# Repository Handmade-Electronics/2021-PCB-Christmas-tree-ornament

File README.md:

# 2021 Snowflake PCB Christmas tree ornament
 Snowflake shaped PCB Christmas tree ornament using a rechargable LIPO battery that recharcges via USB

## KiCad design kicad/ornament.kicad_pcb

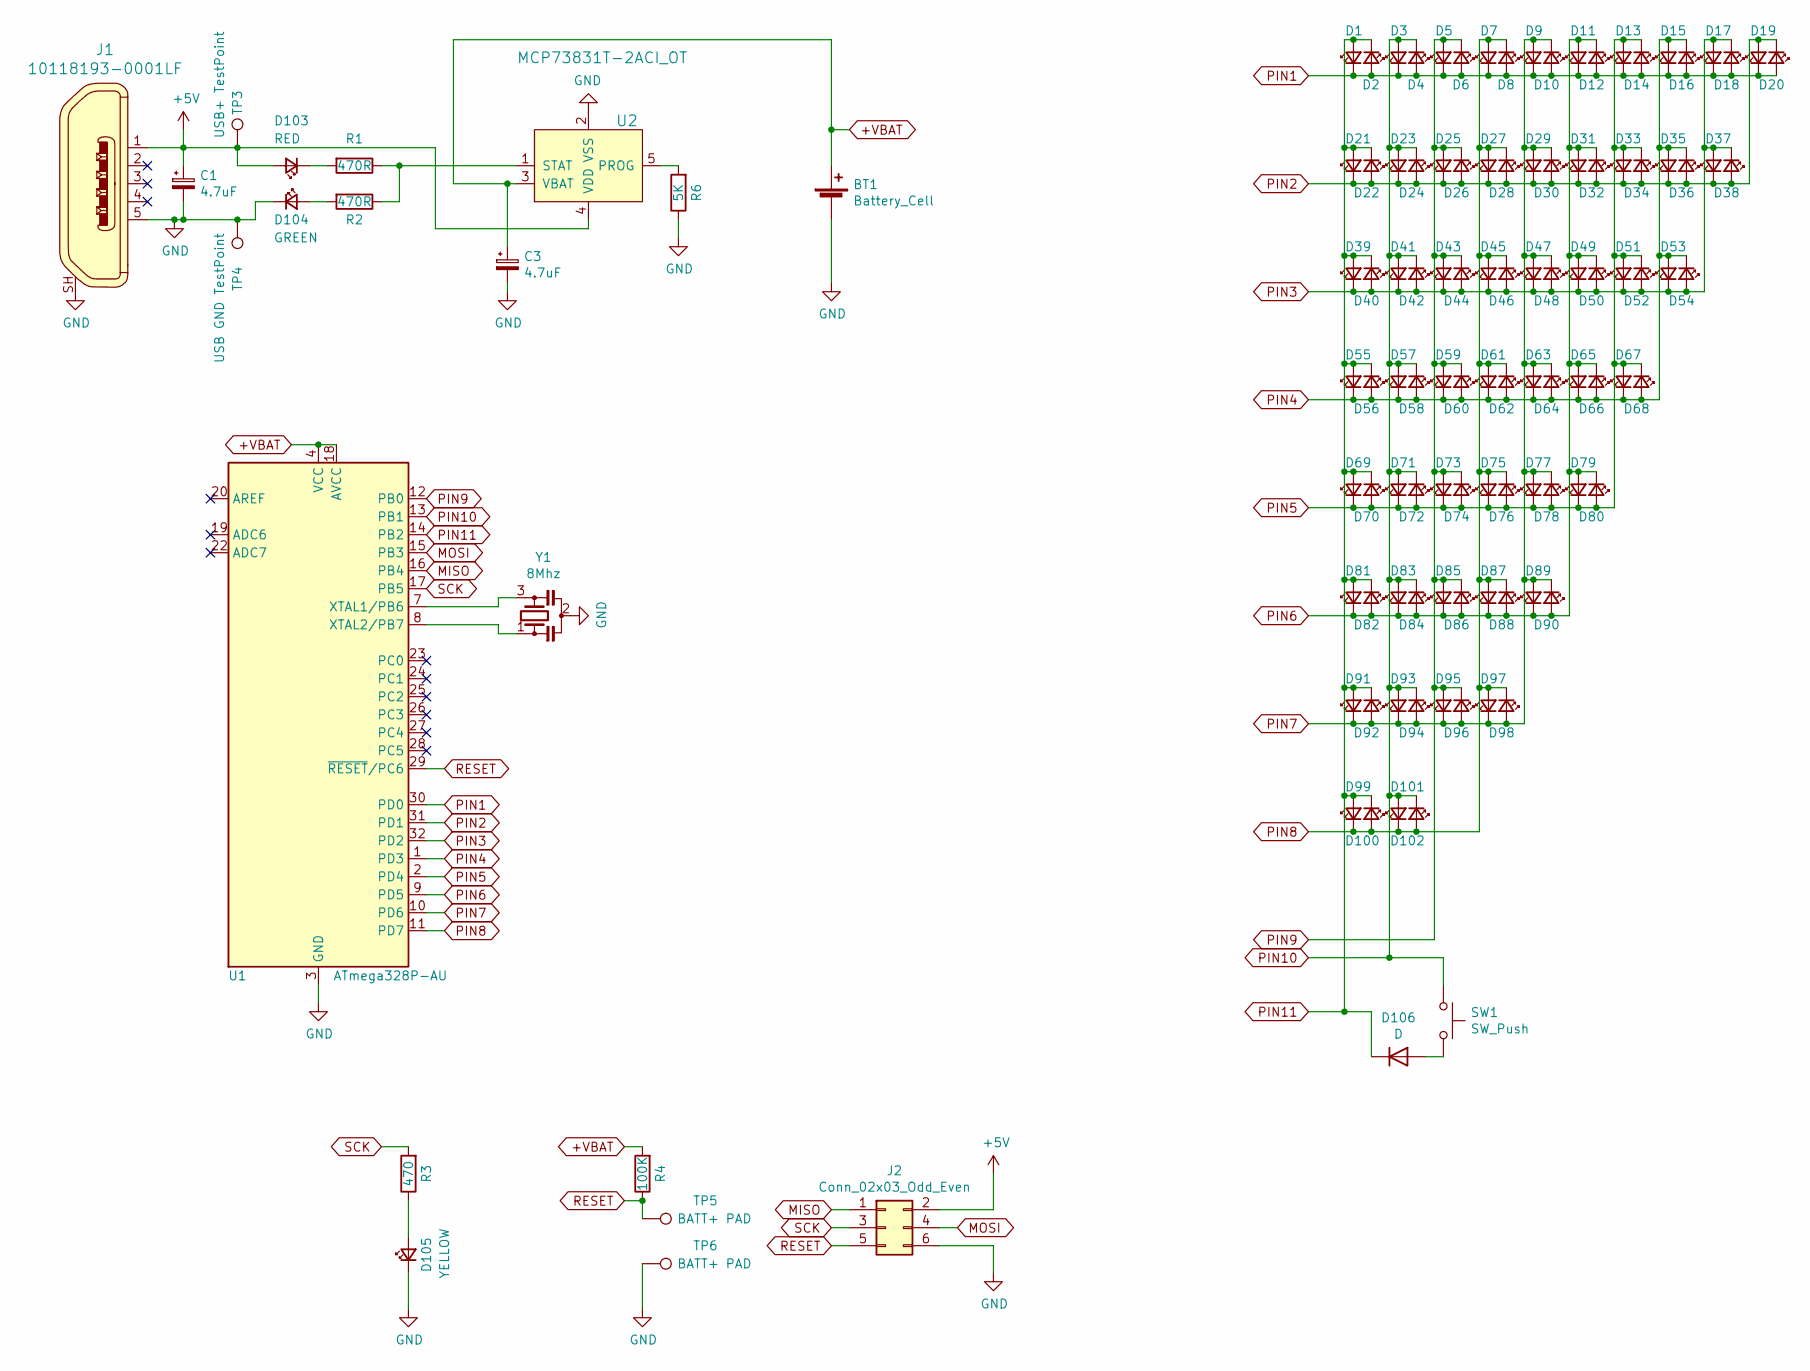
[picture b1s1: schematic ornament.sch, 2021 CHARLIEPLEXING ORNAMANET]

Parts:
BT1: Battery_Cell; LIPO_1S_503030_450mAH
C1, C3: 4.7uF; C_0603_1608Metric_Pad1.08x0.95mm_HandSolder
D1, D2, D3, D4, D5, D6, D7, D8, D9, D10, D11, D12, D13, D14, D15, D16, D17, D18, D19, D20, D21, D22, D23, D24, D25, D26, D27, D28, D29, D30, D31, D32, D33, D34, D35, D36, D37, D38, D39, D40, D41, D42, D43, D44, D45, D46, D47, D48, D49, D50, D51, D52, D53, D54, D55, D56, D57, D58, D59, D60, D61, D62, D63, D64, D65, D66, D67, D68, D69, D70, D71, D72, D73, D74, D75, D76, D77, D78, D79, D80, D81, D82, D83, D84, D85, D86, D87, D88, D89, D90, D91, D92, D93, D94, D95, D96, D97, D98, D99, D100, D101, D102: LED_Small; LED_0805_2012Metric
D103: RED; D_0603_1608Metric
D104: GREEN; D_0603_1608Metric
D105: YELLOW; D_0603_1608Metric
D106: D; D_0603_1608Metric
J1: 10118193-0001LF; USB_Micro_B_Female_10118192; MPN 10118193-0001LF; Digi-Key_PN 609-4616-1-ND
J2: Conn_02x03_Odd_Even; 6Pin_ICSP_Pads
R1, R2: 470R; R_0603_1608Metric
R3: 470; R_0603_1608Metric
R4: 100K; R_0603_1608Metric
R6: 5K; R_0603_1608Metric
SW1: SW_Push; SW_Push_1P1T_NO_6x6mm_H5.0mm(LCSC#C620316)
TP3: USB+ TestPoint; POGO_CONTACT_PAD_3MM
TP4: USB GND TestPoint; POGO_CONTACT_PAD_3MM
TP5, TP6: BATT+ PAD; TestPoint_Pad_2.0x2.0mm
U1: ATmega328P-AU; TQFP-32_7x7mm_P0.8mm
U2: MCP73831T-2ACI_OT; SOT-753; MPN MCP73831T-2ACI/OT; Digi-Key_PN MCP73831T-2ACI/OTCT-ND
Y1: 8Mhz; 3.7x3.1mm_Resonator

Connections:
+5V: C1.1, D103.2 (A), J1.1, J2.2, TP3.1, U2.4 (VDD)
+VBAT: BT1.1 (+), C3.1, R4.2, U1.4 (VCC), U1.6 (VCC), U1.18 (AVCC), U2.3 (VBAT)
GND: BT1.2 (-), C1.2, C3.2, D104.1 (K), D105.1 (K), J1.5, J1.SH, J2.6, R6.1, TP4.1, TP6.1, U1.3 (GND), U1.5 (GND), U1.21 (GND), U2.2 (VSS), Y1.2
MISO: J2.1, U1.16 (PB4)
MOSI: J2.4, U1.15 (PB3)
unnamed: D103.1 (K), R1.2
unnamed: D104.2 (A), R2.2
unnamed: D105.2 (A), R3.1
unnamed: D106.2 (A), SW1.2
unnamed: R1.1, R2.1, U2.1 (STAT)
unnamed: R6.2, U2.5 (PROG)
unnamed: U1.7 (XTAL1/PB6), Y1.3
unnamed: U1.8 (XTAL2/PB7), Y1.1
PIN1: D1.1 (K), D2.2 (A), D3.1 (K), D4.2 (A), D5.1 (K), D6.2 (A), D7.1 (K), D8.2 (A), D9.1 (K), D10.2 (A), D11.1 (K), D12.2 (A), D13.1 (K), D14.2 (A), D15.1 (K), D16.2 (A), D17.1 (K), D18.2 (A), D19.1 (K), D20.2 (A), U1.30 (PD0)
PIN2: D19.2 (A), D20.1 (K), D21.1 (K), D22.2 (A), D23.1 (K), D24.2 (A), D25.1 (K), D26.2 (A), D27.1 (K), D28.2 (A), D29.1 (K), D30.2 (A), D31.1 (K), D32.2 (A), D33.1 (K), D34.2 (A), D35.1 (K), D36.2 (A), D37.1 (K), D38.2 (A), U1.31 (PD1)
PIN3: D17.2 (A), D18.1 (K), D37.2 (A), D38.1 (K), D39.1 (K), D40.2 (A), D41.1 (K), D42.2 (A), D43.1 (K), D44.2 (A), D45.1 (K), D46.2 (A), D47.1 (K), D48.2 (A), D49.1 (K), D50.2 (A), D51.1 (K), D52.2 (A), D53.1 (K), D54.2 (A), U1.32 (PD2)
PIN4: D15.2 (A), D16.1 (K), D35.2 (A), D36.1 (K), D53.2 (A), D54.1 (K), D55.1 (K), D56.2 (A), D57.1 (K), D58.2 (A), D59.1 (K), D60.2 (A), D61.1 (K), D62.2 (A), D63.1 (K), D64.2 (A), D65.1 (K), D66.2 (A), D67.1 (K), D68.2 (A), U1.1 (PD3)
PIN5: D13.2 (A), D14.1 (K), D33.2 (A), D34.1 (K), D51.2 (A), D52.1 (K), D67.2 (A), D68.1 (K), D69.1 (K), D70.2 (A), D71.1 (K), D72.2 (A), D73.1 (K), D74.2 (A), D75.1 (K), D76.2 (A), D77.1 (K), D78.2 (A), D79.1 (K), D80.2 (A), U1.2 (PD4)
PIN6: D11.2 (A), D12.1 (K), D31.2 (A), D32.1 (K), D49.2 (A), D50.1 (K), D65.2 (A), D66.1 (K), D79.2 (A), D80.1 (K), D81.1 (K), D82.2 (A), D83.1 (K), D84.2 (A), D85.1 (K), D86.2 (A), D87.1 (K), D88.2 (A), D89.1 (K), D90.2 (A), U1.9 (PD5)
PIN7: D9.2 (A), D10.1 (K), D29.2 (A), D30.1 (K), D47.2 (A), D48.1 (K), D63.2 (A), D64.1 (K), D77.2 (A), D78.1 (K), D89.2 (A), D90.1 (K), D91.1 (K), D92.2 (A), D93.1 (K), D94.2 (A), D95.1 (K), D96.2 (A), D97.1 (K), D98.2 (A), U1.10 (PD6)
PIN8: D7.2 (A), D8.1 (K), D27.2 (A), D28.1 (K), D45.2 (A), D46.1 (K), D61.2 (A), D62.1 (K), D75.2 (A), D76.1 (K), D87.2 (A), D88.1 (K), D97.2 (A), D98.1 (K), D99.1 (K), D100.2 (A), D101.1 (K), D102.2 (A), U1.11 (PD7)
PIN9: D5.2 (A), D6.1 (K), D25.2 (A), D26.1 (K), D43.2 (A), D44.1 (K), D59.2 (A), D60.1 (K), D73.2 (A), D74.1 (K), D85.2 (A), D86.1 (K), D95.2 (A), D96.1 (K), U1.12 (PB0)
PIN10: D3.2 (A), D4.1 (K), D23.2 (A), D24.1 (K), D41.2 (A), D42.1 (K), D57.2 (A), D58.1 (K), D71.2 (A), D72.1 (K), D83.2 (A), D84.1 (K), D93.2 (A), D94.1 (K), D101.2 (A), D102.1 (K), SW1.1, U1.13 (PB1)
PIN11: D1.2 (A), D2.1 (K), D21.2 (A), D22.1 (K), D39.2 (A), D40.1 (K), D55.2 (A), D56.1 (K), D69.2 (A), D70.1 (K), D81.2 (A), D82.1 (K), D91.2 (A), D92.1 (K), D99.2 (A), D100.1 (K), D106.1 (K), U1.14 (PB2)
RESET: J2.5, R4.1, TP5.1, U1.29 (~RESET~/PC6)
SCK: J2.3, R3.2, U1.17 (PB5)

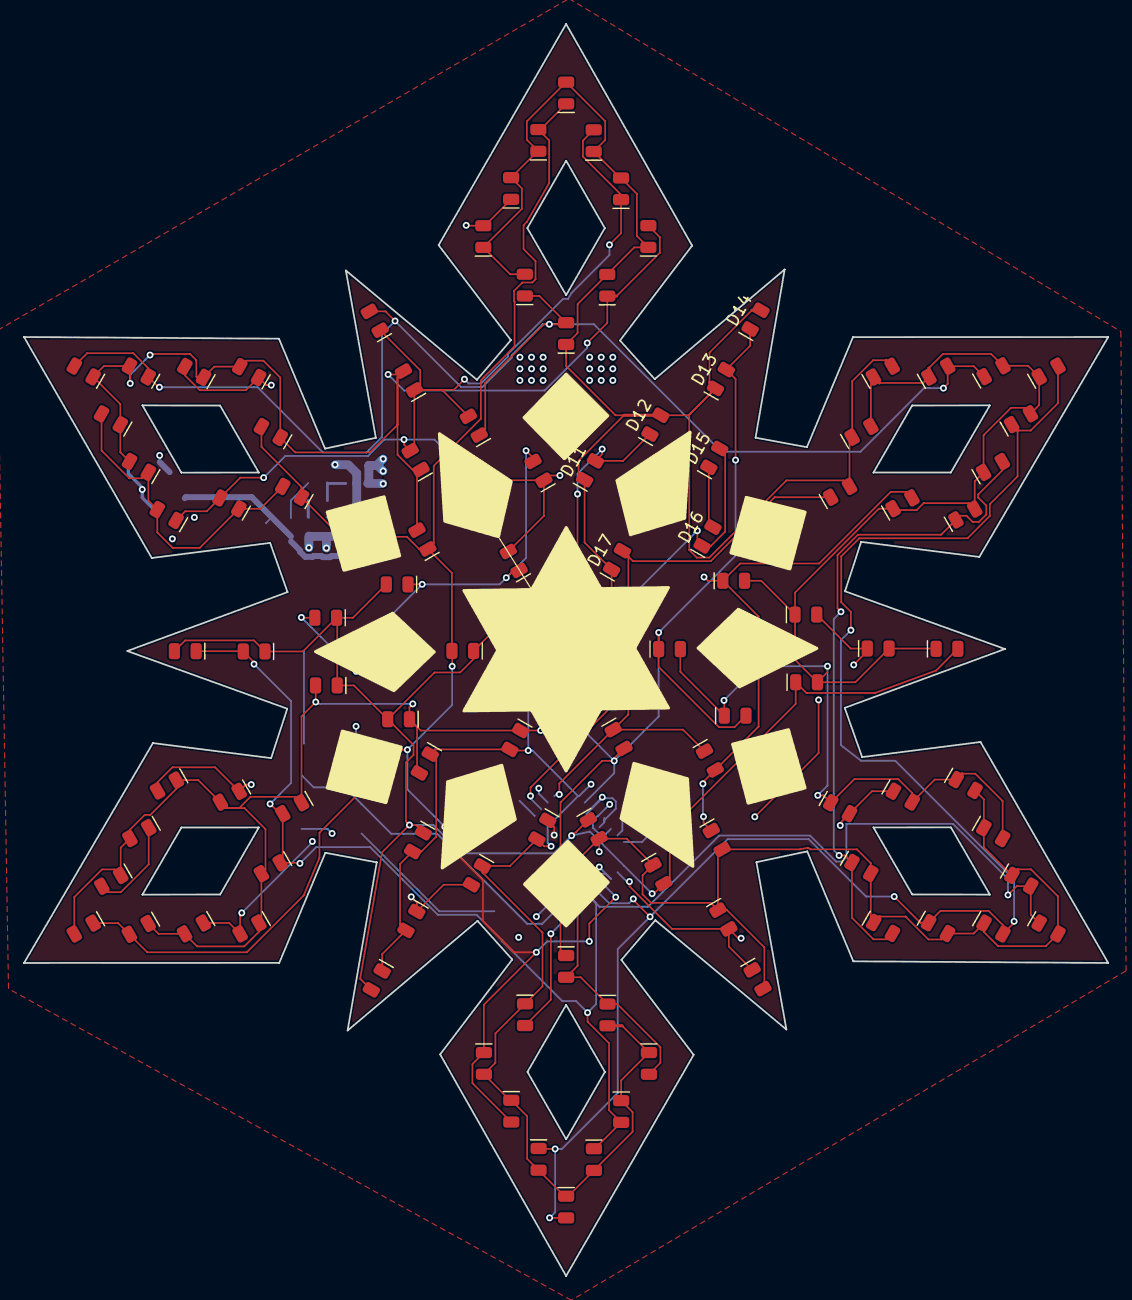
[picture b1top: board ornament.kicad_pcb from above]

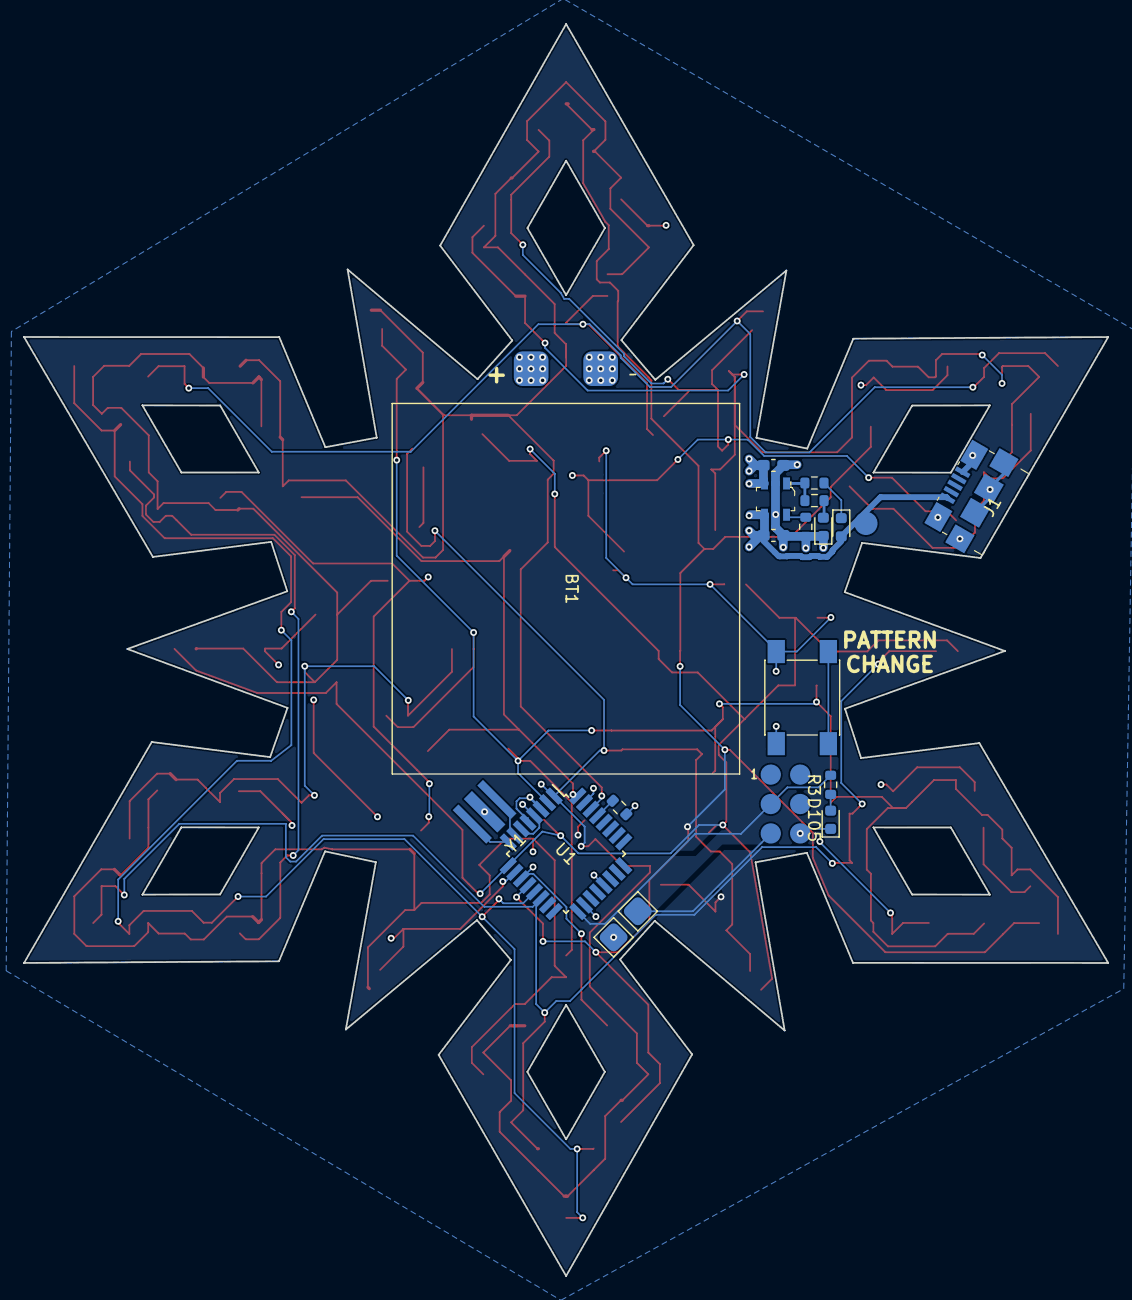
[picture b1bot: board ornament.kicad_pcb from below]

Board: 4 copper layers, 93.6 x 108.1 mm, 122 parts (20 on the bottom side), 25 nets.

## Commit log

2021-01-18 uploaded initial working files
2021-01-18 Update issue templates
2021-01-19 Set theme jekyll-theme-slate
2021-01-19 18 Jan working update
2021-01-19 created port settings and display buffers
    Port settings are used to turn LEDs on and off.
    Buffers are used to display LEDs in a particular pattern.
2021-01-20 jan18 revisions
2021-01-20 renamed files
    from star to ornament
2021-01-23 23JAN2021
    90% PCB layout
